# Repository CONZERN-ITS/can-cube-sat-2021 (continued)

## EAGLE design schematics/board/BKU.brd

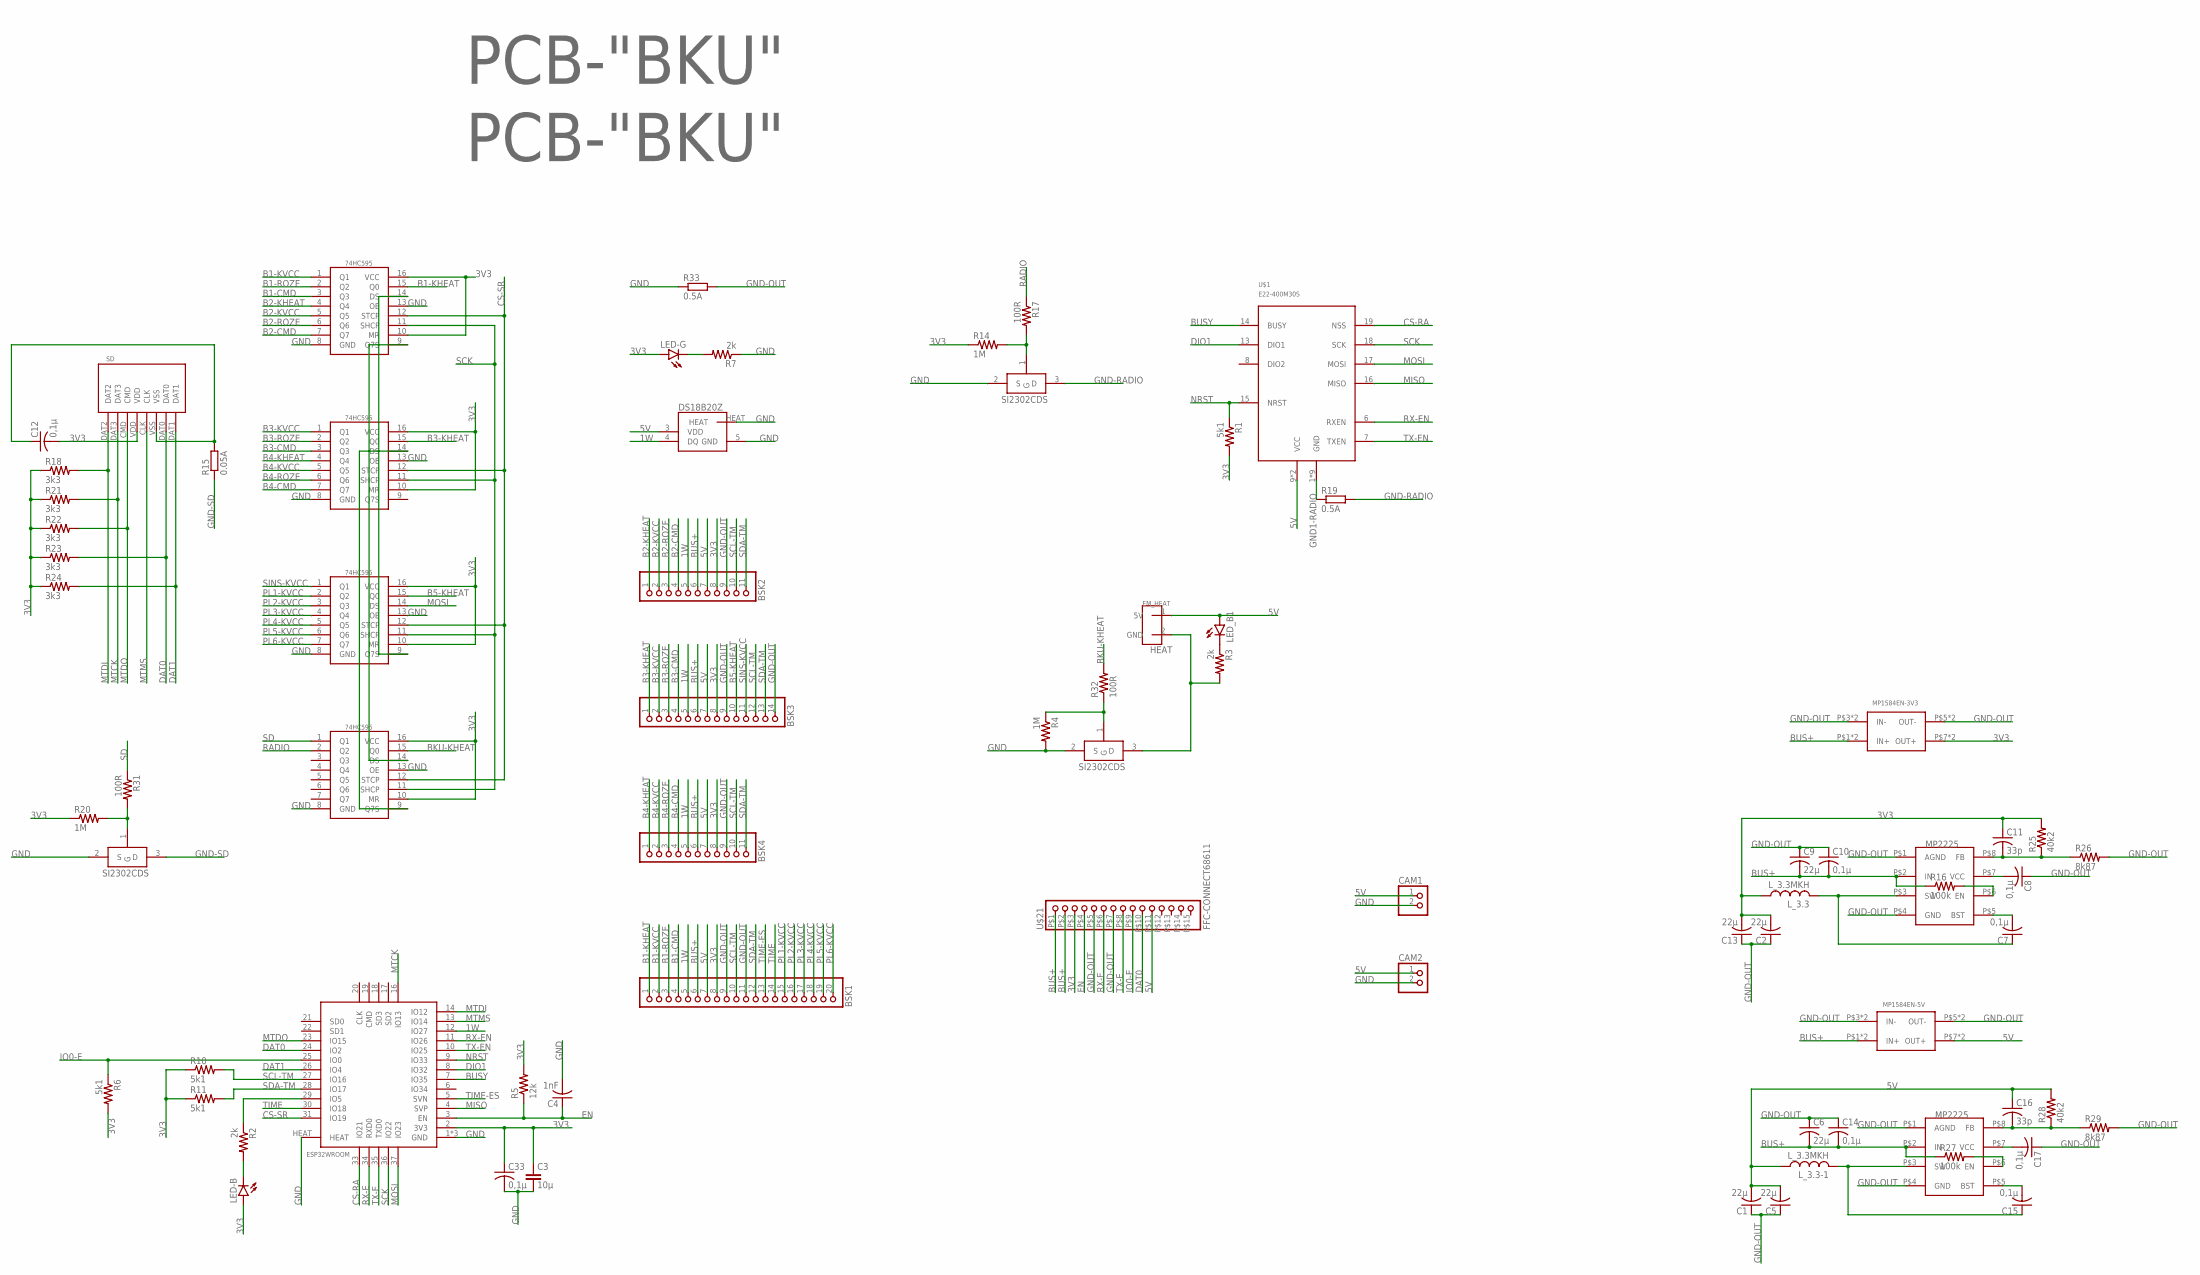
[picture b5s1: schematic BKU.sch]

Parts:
74HC595#1, 74HC595#2, 74HC595#3, 74HC595#4: 74HC595; TSSOP16
BSK1: PINHD-1X20; 1X20
BSK2, BSK4: PINHD-1X11; 1X11
BSK3: PINHD-1X14; 1X14
C1, C2, C5, C6, C9, C13: 22µ; C1206
C3: 10µ; C1206
C4: 1nF; C0603
C7, C8, C10, C12, C14, C15, C17, C33: 0,1µ; C0603
C11, C16: 33p; C0603
CAM1, CAM2: PINHD-1X2; 1X02
LED-B: LEDCHIPLED_0603; CHIPLED_0603
LED-G: LEDCHIPLED_0603; CHIPLED_0603
LED_B1: LEDCHIPLED_0603; CHIPLED_0603
L_3.3, L_3.3-1: L_3.3MKH; L_SPM5020
MP1584EN-3V3, MP1584EN-5V: MP1584-B
MP2225-3V3, MP2225-5V: MP2225; TSOT23-8
R1, R6, R10, R11: 5k1; R0603
R2, R3, R7: 2k; R0603
R4, R14, R20: 1M; R0603
R5: 12k; R0603
R15: 0.05A; R1210
R16, R27: 100k; R0603
R17, R31, R32: 100R; R0603
R18, R21, R22, R23, R24: 3k3; R0603
R19, R33: 0.5A; R1210
R25, R28: 40k2; R0603
R26, R29: 8k87; R0603
SD: SD
U$1: E22-400M30S
U$2, U$6: PCB-"BKU"; ITS-LOGO
U$3, U$4, U$23: SI2302CDS; SOT23-3
U$5: DS18B20Z; SOIC8+HEAT_S
U$13: ESP32WROOM
U$21: FFC-CONNECT68611; 68611
U$24: EM_HEAT

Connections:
1W: BSK1.5, BSK2.5, BSK3.5, BSK4.5, U$5.4 (DQ), U$13.12 (IO27)
3: R3.2, U$23.3 (D), U$24.2 (GND)
3V3: 74HC595#1.10 (MR), 74HC595#1.16 (VCC), 74HC595#2.10 (MR), 74HC595#2.16 (VCC), 74HC595#3.10 (MR), 74HC595#3.16 (VCC), 74HC595#4.10 (MR), 74HC595#4.16 (VCC), BSK1.8, BSK2.8, BSK3.8, BSK4.8, C2.2, C3.1, C11.1, C12.2, C13.2, C33.1, LED-B.A, LED-G.A, L_3.3.P$1 (1), MP1584EN-3V3.P$7 (OUT+), MP1584EN-3V3.P$8 (OUT+), R1.2, R5.2, R6.2, R10.1, R11.1, R14.1, R18.1, R20.1, R21.1, R22.1, R23.1, R24.1, R25.2, SD.VDD, U$13.2 (3V3), U$21.P$3 (3)
5V: BSK1.7, BSK2.7, BSK3.7, BSK4.7, C1.2, C5.2, C16.1, CAM1.1, CAM2.1, LED_B1.A, L_3.3-1.P$1 (1), MP1584EN-5V.P$7 (OUT+), MP1584EN-5V.P$8 (OUT+), R28.2, U$1.9 (VCC), U$1.10 (VCC), U$5.3 (VDD), U$21.P$11 (11), U$24.1 (5V)
B1-CMD: 74HC595#1.3 (Q3), BSK1.4
B1-KHEAT: 74HC595#1.15 (Q0), BSK1.1
B1-KVCC: 74HC595#1.1 (Q1), BSK1.2
B1-ROZE: 74HC595#1.2 (Q2), BSK1.3
B2-CMD: 74HC595#1.7 (Q7), BSK2.4
B2-KHEAT: 74HC595#1.4 (Q4), BSK2.1
B2-KVCC: 74HC595#1.5 (Q5), BSK2.2
B2-ROZE: 74HC595#1.6 (Q6), BSK2.3
B3-CMD: 74HC595#2.3 (Q3), BSK3.4
B3-KHEAT: 74HC595#2.15 (Q0), BSK3.1
B3-KVCC: 74HC595#2.1 (Q1), BSK3.2
B3-ROZE: 74HC595#2.2 (Q2), BSK3.3
B4-CMD: 74HC595#2.7 (Q7), BSK4.4
B4-KHEAT: 74HC595#2.4 (Q4), BSK4.1
B4-KVCC: 74HC595#2.5 (Q5), BSK4.2
B4-ROZE: 74HC595#2.6 (Q6), BSK4.3
B5-KHEAT: 74HC595#3.15 (Q0), BSK3.10
BKU-KHEAT: 74HC595#4.15 (Q0), R32.2
BUS+: BSK1.6, BSK2.6, BSK3.6, BSK4.6, C6.2, C9.2, C10.2, C14.2, MP1584EN-3V3.P$1 (IN+), MP1584EN-3V3.P$2 (IN+), MP1584EN-5V.P$1 (IN+), MP1584EN-5V.P$2 (IN+), MP2225-3V3.P$2 (IN), MP2225-5V.P$2 (IN), R16.1, R27.1, U$21.P$1 (1), U$21.P$2 (2)
BUSY: U$1.14 (BUSY), U$13.7 (IO35)
CS-RA: U$1.19 (NSS), U$13.33 (IO21)
CS-SR: 74HC595#1.12 (STCP), 74HC595#2.12 (STCP), 74HC595#3.12 (STCP), 74HC595#4.12 (STCP), U$13.31 (IO19)
DAT0: R23.2, SD.DAT0, U$13.24 (IO2), U$21.P$10 (10)
DAT1: R24.2, SD.DAT1, U$13.26 (IO4)
DIO1: U$1.13 (DIO1), U$13.8 (IO32)
EN: C4.1, R5.1, U$13.3 (EN), U$21.P$4 (4)
GND: 74HC595#1.8 (GND), 74HC595#1.13 (OE), 74HC595#2.8 (GND), 74HC595#2.13 (OE), 74HC595#3.8 (GND), 74HC595#3.13 (OE), 74HC595#4.8 (GND), 74HC595#4.13 (OE), C3.2, C4.2, C33.2, CAM1.2, CAM2.2, R4.2, R7.1, R33.1, U$3.2 (S), U$4.2 (S), U$5.5 (GND), U$5.HEAT, U$13.1 (GND), U$13.15 (GND), U$13.38 (GND), U$13.HEAT, U$23.2 (S)
GND1-RADIO: R19.1, U$1.1 (GND), U$1.2 (GND), U$1.3 (GND), U$1.4 (GND), U$1.5 (GND), U$1.11 (GND), U$1.12 (GND), U$1.20 (GND), U$1.22 (GND)
GND-OUT: BSK1.9, BSK1.11, BSK2.9, BSK3.9, BSK3.14, BSK4.9, C1.1, C2.1, C5.1, C6.1, C8.1, C9.1, C10.1, C13.1, C14.1, C17.1, MP1584EN-3V3.P$3 (IN-), MP1584EN-3V3.P$4 (IN-), MP1584EN-3V3.P$5 (OUT-), MP1584EN-3V3.P$6 (OUT-), MP1584EN-5V.P$3 (IN-), MP1584EN-5V.P$4 (IN-), MP1584EN-5V.P$5 (OUT-), MP1584EN-5V.P$6 (OUT-), MP2225-3V3.P$1 (AGND), MP2225-3V3.P$4 (GND), MP2225-5V.P$1 (AGND), MP2225-5V.P$4 (GND), R26.2, R29.2, R33.2, U$21.P$5 (5), U$21.P$7 (7)
GND-RADIO: R19.2, U$4.3 (D)
GND-SD: R15.1, U$3.3 (D)
IO0-E: R6.1, U$13.25 (IO0), U$21.P$9 (9)
IO1: R2.1, U$13.29 (IO5)
MISO: U$1.16 (MISO), U$13.4 (SVP)
MOSI: 74HC595#3.14 (DS), U$1.17 (MOSI), U$13.37 (IO23)
MTCK: R21.2, SD.DAT3, U$13.16 (IO13)
MTDI: R18.2, SD.DAT2, U$13.14 (IO12)
MTDO: R22.2, SD.CMD, U$13.23 (IO15)
MTMS: SD.CLK, U$13.13 (IO14)
unnamed: 74HC595#1.9 (Q7S), 74HC595#4.14 (DS)
unnamed: LED_B1.C, R3.1
unnamed: LED-G.C, R7.2
unnamed: LED-B.C, R2.2
unnamed: C12.1, R15.2, SD.VSS
unnamed: R14.2, R17.2, U$4.1 (G)
unnamed: 74HC595#2.14 (DS), 74HC595#4.9 (Q7S)
unnamed: C15.1, L_3.3-1.P$2 (2), MP2225-5V.P$3 (SW)
unnamed: C15.2, MP2225-5V.P$5 (BST)
unnamed: MP2225-5V.P$6 (EN), R27.2
unnamed: R20.2, R31.2, U$3.1 (G)
unnamed: C17.2, MP2225-5V.P$7 (VCC)
unnamed: C7.2, MP2225-3V3.P$5 (BST)
unnamed: C7.1, L_3.3.P$2 (2), MP2225-3V3.P$3 (SW)
unnamed: MP2225-3V3.P$6 (EN), R16.2
unnamed: C8.2, MP2225-3V3.P$7 (VCC)
unnamed: 74HC595#1.14 (DS), 74HC595#3.9 (Q7S)
unnamed: C11.2, MP2225-3V3.P$8 (FB), R25.1, R26.1
unnamed: C16.2, MP2225-5V.P$8 (FB), R28.1, R29.1
unnamed: R4.1, R32.1, U$23.1 (G)
NRST: R1.1, U$1.15 (NRST), U$13.9 (IO33)
PL1-KVCC: 74HC595#3.2 (Q2), BSK1.15
PL2-KVCC: 74HC595#3.3 (Q3), BSK1.16
PL3-KVCC: 74HC595#3.4 (Q4), BSK1.17
PL4-KVCC: 74HC595#3.5 (Q5), BSK1.18
PL5-KVCC: 74HC595#3.6 (Q6), BSK1.19
PL6-KVCC: 74HC595#3.7 (Q7), BSK1.20
RADIO: 74HC595#4.2 (Q2), R17.1
RX-E: U$13.34 (RXD0), U$21.P$6 (6)
RX-EN: U$1.6 (RXEN), U$13.11 (IO26)
SCK: 74HC595#1.11 (SHCP), 74HC595#2.11 (SHCP), 74HC595#3.11 (SHCP), 74HC595#4.11 (SHCP), U$1.18 (SCK), U$13.36 (IO22)
SCL-TM: BSK1.10, BSK2.10, BSK3.12, BSK4.10, R10.2, U$13.27 (IO16)
SD: 74HC595#4.1 (Q1), R31.1
SDA-TM: BSK1.12, BSK2.11, BSK3.13, BSK4.11, R11.2, U$13.28 (IO17)
SINS-KVCC: 74HC595#3.1 (Q1), BSK3.11
TIME: BSK1.14, U$13.30 (IO18)
TIME-ES: BSK1.13, U$13.5 (SVN)
TX-E: U$13.35 (TXD0), U$21.P$8 (8)
TX-EN: U$1.7 (TXEN), U$13.10 (IO25)

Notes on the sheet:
HEAT

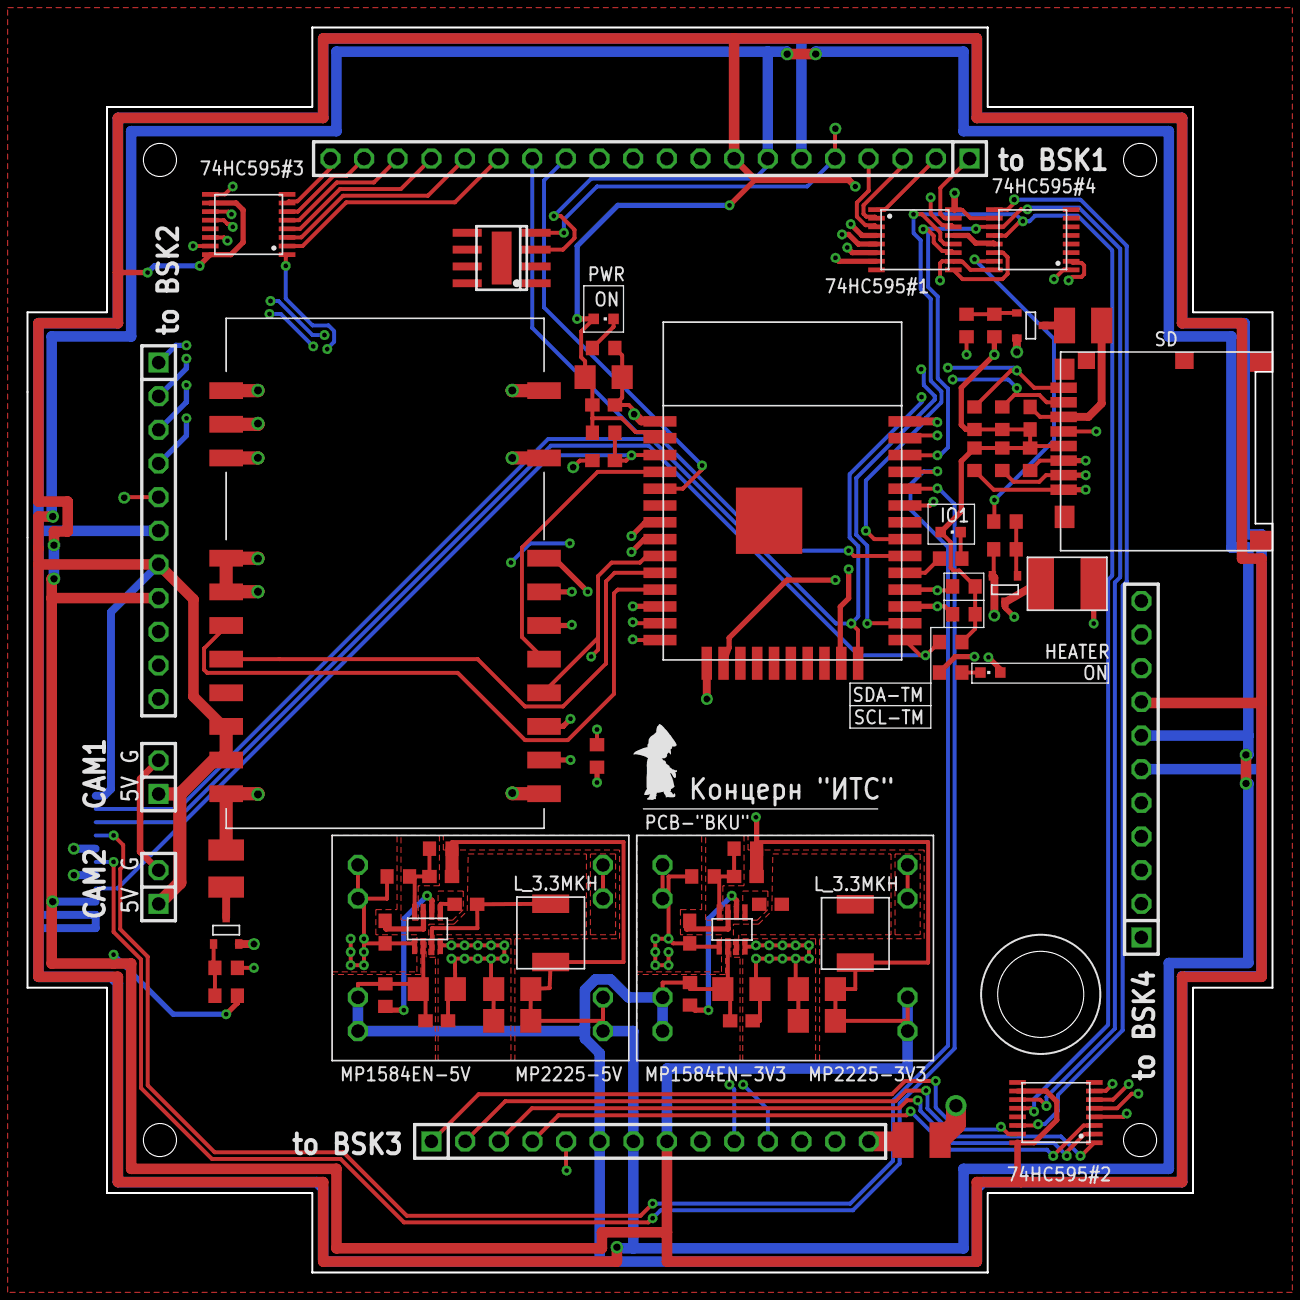
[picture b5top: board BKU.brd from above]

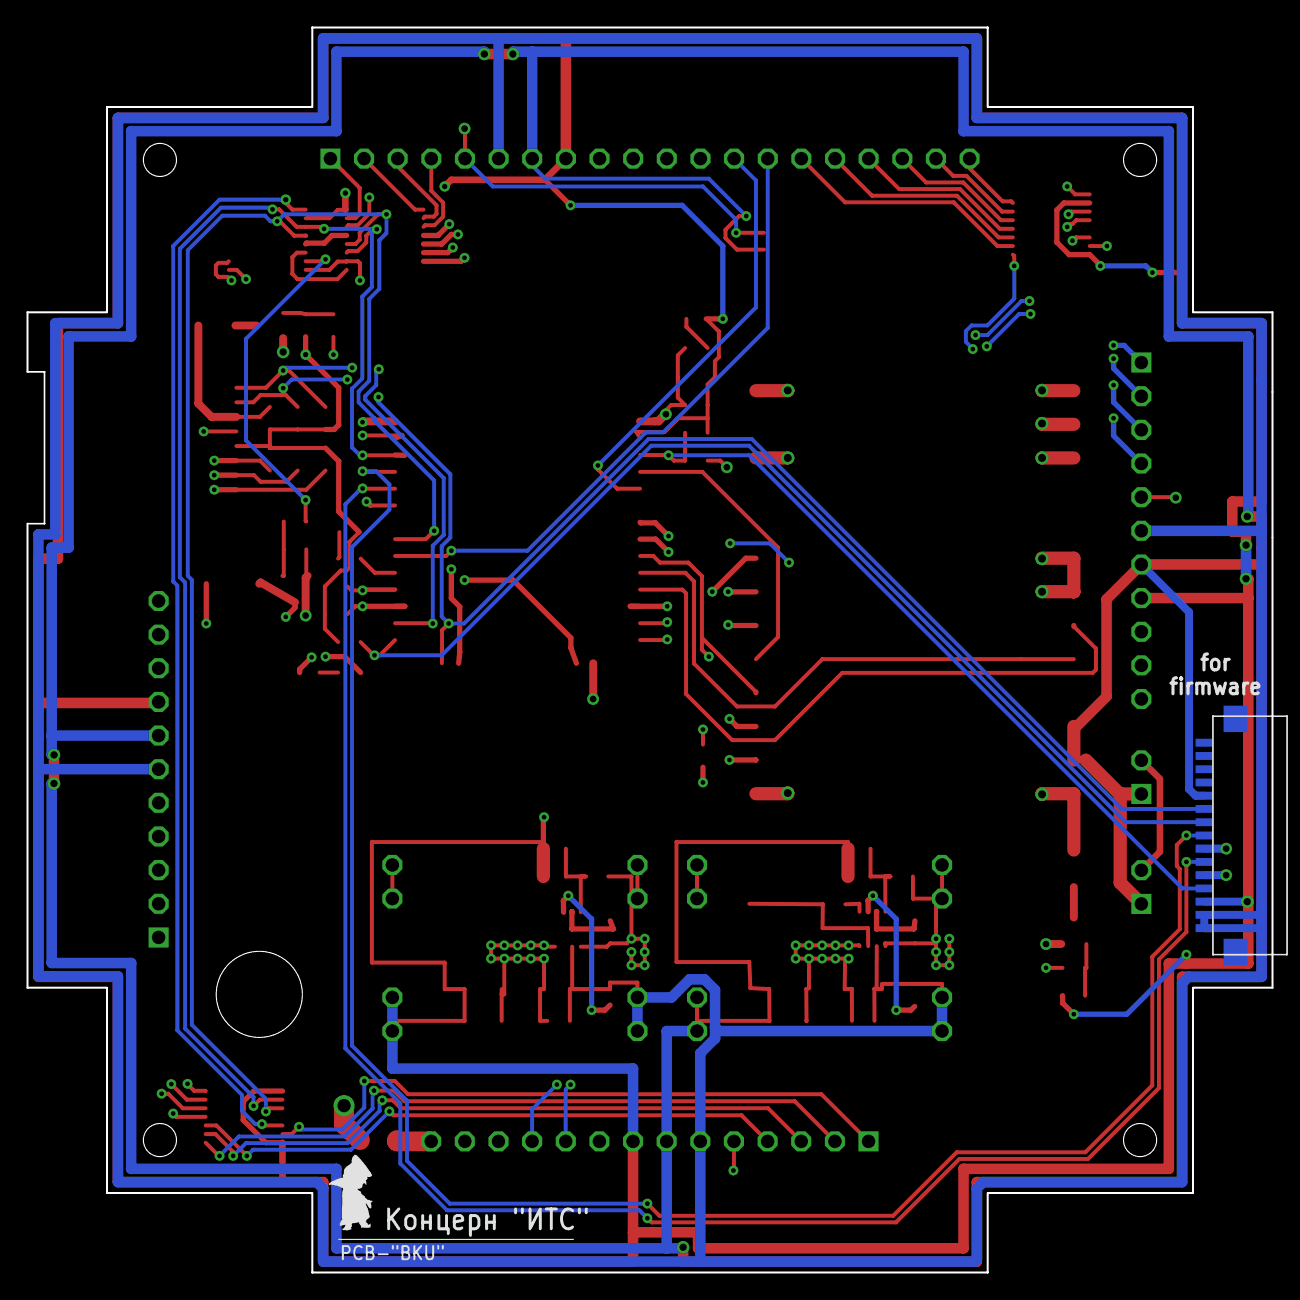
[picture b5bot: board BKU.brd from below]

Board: 4 copper layers, 94.0 x 94.0 mm, 76 parts (2 on the bottom side), 82 nets.

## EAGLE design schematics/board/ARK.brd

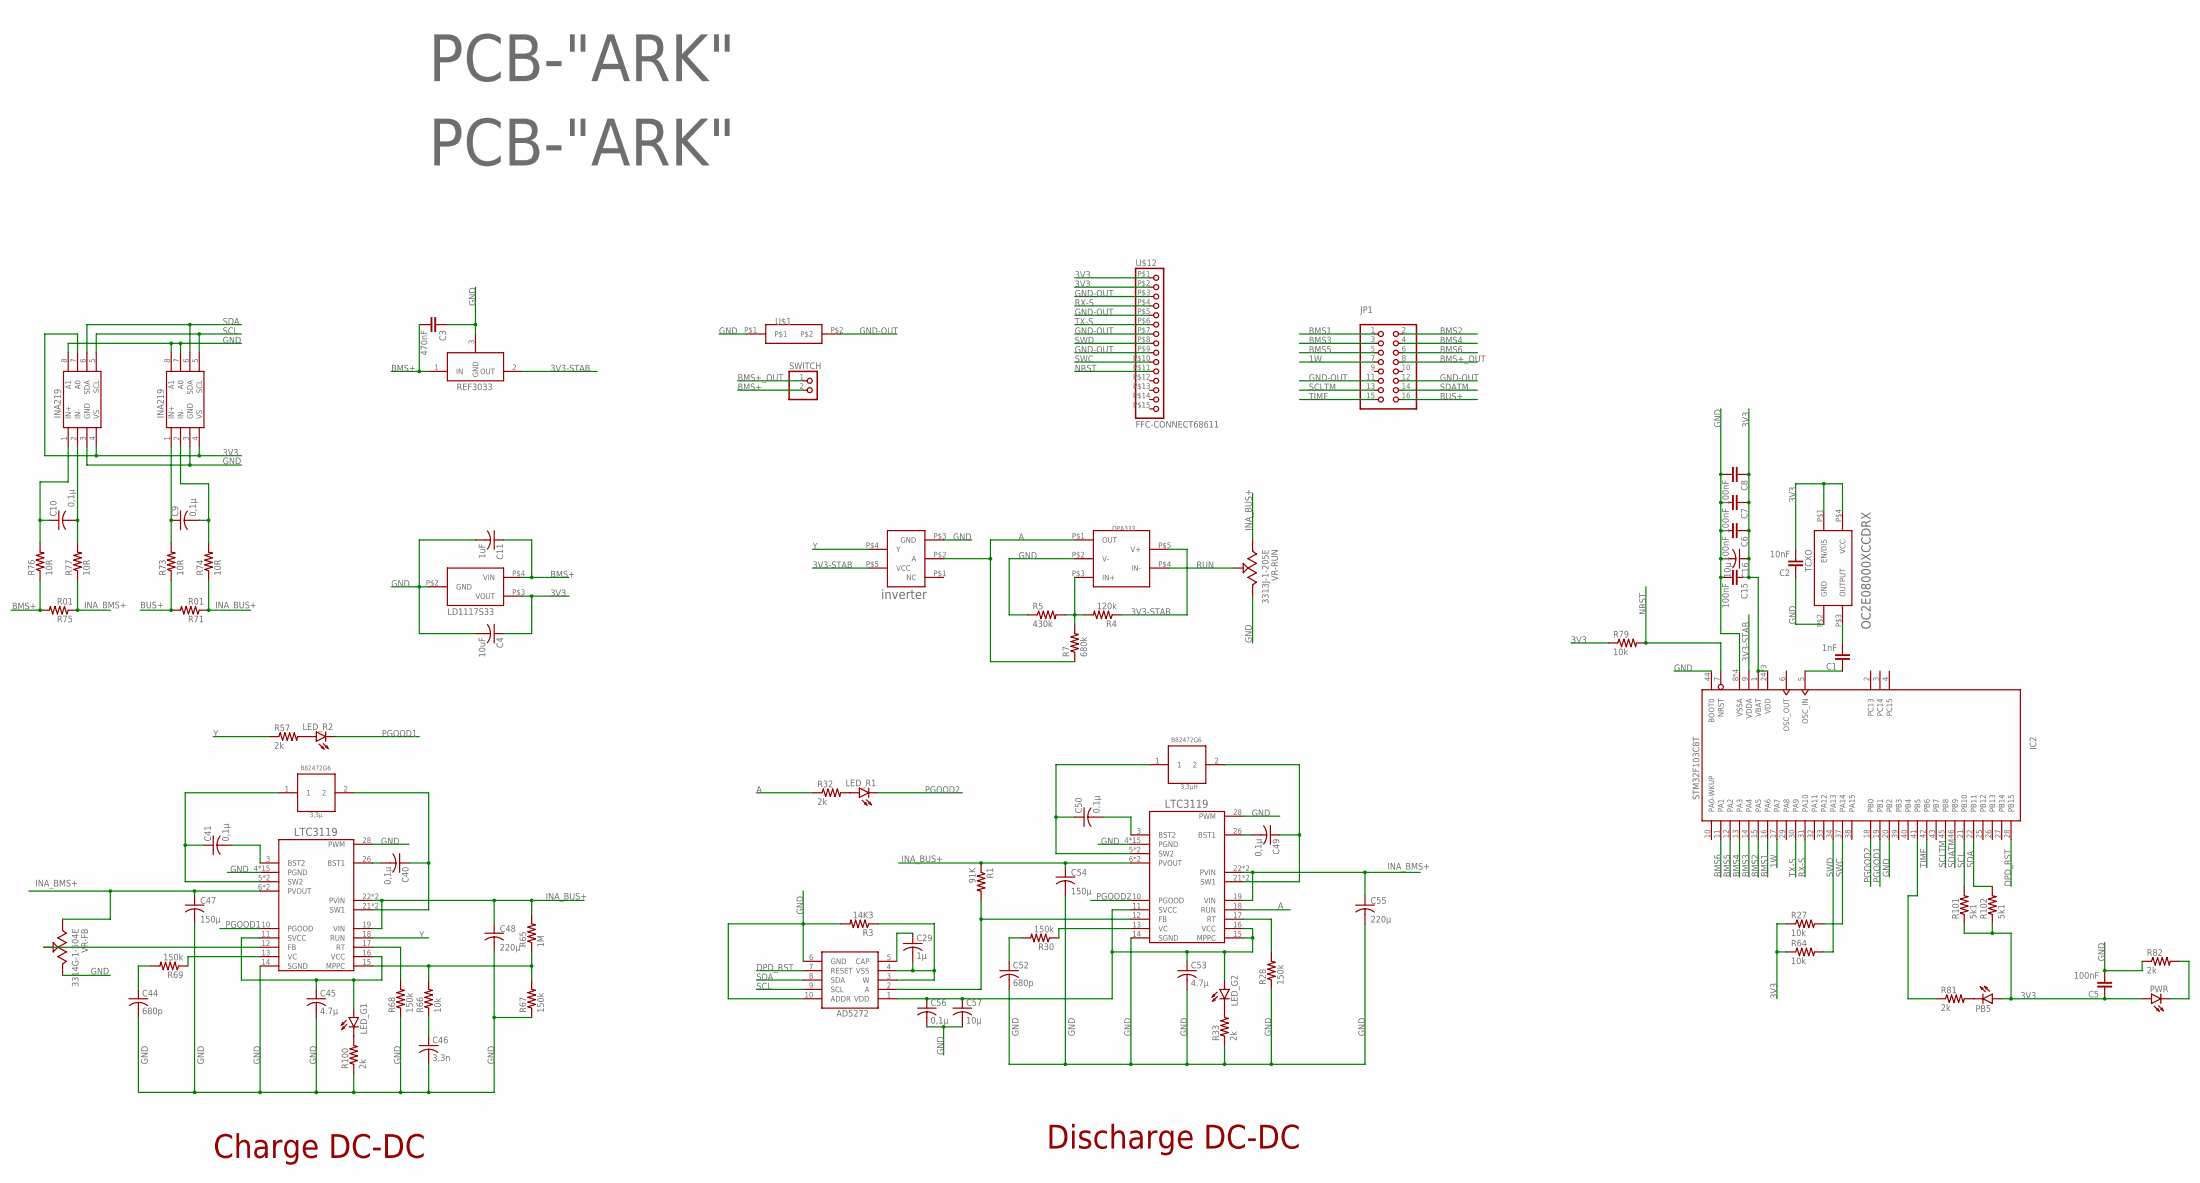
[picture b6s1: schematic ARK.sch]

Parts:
3,3µH: 3,3µ; B82472G6
3,3µH1: 3,3µH; B82472G6
AD5272#2: AD5272; MSOP10
C1: 1nF; C0603
C2: 10nF; C0603
C3: 470nF; C0603
C4: 10uF; ECAP-SMD-D4
C5, C6, C7, C8, C15: 100nF; C0603
C9, C10, C40, C41, C49, C50, C56: 0,1µ; C0603
C11: 1uF; ECAP-SMD-D4
C16, C57: 10µ; C1206
C29: 1µ; C0603
C44, C52: 680p; C0603
C45, C53: 4.7µ; C1206
C46: 3,3n; C0603
C47, C54: 150µ; ECAP150-CMD
C48, C55: 220µ; ECAP220-CMD
IC2: STM32F103C8T; LQFP48
INA219#1, INA219#2: INA219AID; SOT23-8
INVERT: INVERTER.; SC70
JP1: PINHD-2X8; 2X08
LD1117S33: LD1117S33; SOT223
LED_G1, LED_G2: LEDCHIPLED_0603; CHIPLED_0603
LED_R1, LED_R2: LEDCHIPLED_0603; CHIPLED_0603
OPA: OPA333; SOT23-5
PB5: LEDCHIPLED_0603; CHIPLED_0603
PWR: LEDCHIPLED_0603; CHIPLED_0603
R1: 91K; R0603
R3: 14K3; R0603
R4: 120k; R0603
R5: 430k; R0603
R7: 680k; R0603
R27, R64, R66, R79: 10k; R0603
R28, R30, R67, R68, R69: 150k; R0603
R32, R33, R57, R81, R82, R100: 2k; R0603
R65: 1M; R0603
R71, R75: R01; R2512
R73, R74, R76, R77: 10R; R0603
R101, R102: 5k1; R0603
REF3033: REF3033; SOT23-3
SWITCH: PINHD-1X2; 1X02
TCXO: OC2E08000XCCDRX
U$1: MF-R400
U$3, U$4: PCB-"ARK"; ITS-LOGO
U$12: FFC-CONNECT68611; 68611
U$23, U$59: LTC31191; LTC3119+VIA
VR-FB: 3314G-1-504E; TRIM_3314G-1-504E
VR-RUN: 3313J-1-205E; TRIM_3313J-1-205E

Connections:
1W: IC2.17 (PA7), JP1.7
3V3: C2.2, C4.P+ (1), C5.1, C6.1, C7.1, C8.1, C15.1, C16.1, IC2.1 (VBAT), IC2.24 (VDD), IC2.36 (VDD), IC2.48 (VDD), INA219#1.4 (VS), INA219#2.4 (VS), INA219#2.7 (A0), LD1117S33.P$3 (VOUT), PB5.A, PWR.A, R27.1, R64.1, R79.1, R101.1, R102.1, TCXO.P$1 (EN/DIS), TCXO.P$4 (VCC), U$12.P$1 (1), U$12.P$2 (2)
3V3-STAB: IC2.9 (VDDA), INVERT.P$5 (VCC), OPA.P$5 (V+), R4.1, REF3033.2 (OUT)
90: R65.1, R66.2, R67.2, U$59.15 (MPPC)
A: INVERT.P$2 (A), OPA.P$1 (OUT), R7.1, R32.1, U$23.18 (RUN)
BMS1: IC2.16 (PA6), JP1.1
BMS2: IC2.15 (PA5), JP1.2
BMS3: IC2.14 (PA4), JP1.3
BMS4: IC2.13 (PA3), JP1.4
BMS5: IC2.12 (PA2), JP1.5
BMS6: IC2.11 (PA1), JP1.6
BMS+: C3.2, C11.P+ (1), LD1117S33.P$4 (VIN), R75.2, R76.1, REF3033.1 (IN), SWITCH.2
BMS+_OUT: JP1.8, SWITCH.1
BUS+: JP1.16, R71.2, R73.1
DPD_RST: AD5272#2.7 (RESET), IC2.28 (PB15)
GND: AD5272#2.6 (GND), AD5272#2.10 (ADDR), C2.1, C3.1, C4.P- (2), C5.2, C6.2, C7.2, C8.2, C11.P- (2), C15.2, C16.2, C44.2, C45.2, C46.2, C47.P$2 (2), C48.P$2 (2), C52.2, C53.2, C54.P$2 (2), C55.P$2 (2), C56.2, C57.2, IC2.8 (VSSA), IC2.20 (PB2), IC2.23 (VSSA), IC2.35 (VSSA), IC2.44 (BOOT0), IC2.47 (VSSA), INA219#1.3 (GND), INA219#1.7 (A0), INA219#1.8 (A1), INA219#2.3 (GND), INA219#2.8 (A1), INVERT.P$3 (GND), LD1117S33.P$2 (GND), OPA.P$2 (V-), R3.2, R5.1, R28.1, R33.1, R67.1, R68.1, R82.1, R100.1, REF3033.3 (GND), TCXO.P$2 (GND), U$1.P$1, U$23.4 (PGND), U$23.9 (PGND), U$23.14 (SGND), U$23.20 (PGND), U$23.25 (PGND), U$23.28 (PWM), U$23.29 (PGND), U$23.P$1 (PGND), U$23.P$2 (PGND), U$23.P$3 (PGND), U$23.P$4 (PGND), U$23.P$5 (PGND), U$23.P$6 (PGND), U$23.P$7 (PGND), U$23.P$8 (PGND), U$23.P$9 (PGND), U$23.P$10 (PGND), U$59.4 (PGND), U$59.9 (PGND), U$59.14 (SGND), U$59.20 (PGND), U$59.25 (PGND), U$59.28 (PWM), U$59.29 (PGND), U$59.P$1 (PGND), U$59.P$2 (PGND), U$59.P$3 (PGND), U$59.P$4 (PGND), U$59.P$5 (PGND), U$59.P$6 (PGND), U$59.P$7 (PGND), U$59.P$8 (PGND), U$59.P$9 (PGND), U$59.P$10 (PGND), VR-FB.3 (CW), VR-RUN.3 (CW)
GND-OUT: JP1.11, JP1.12, U$1.P$2, U$12.P$3 (3), U$12.P$5 (5), U$12.P$7 (7), U$12.P$9 (9)
INA_BMS+: C47.P$1 (1), C55.P$1 (1), R75.1, R77.1, U$23.19 (VIN), U$23.22 (PVIN), U$23.23 (PVIN), U$59.6 (PVOUT), U$59.7 (PVOUT), VR-FB.1 (CCW)
INA_BUS+: C48.P$1 (1), C54.P$1 (1), R1.1, R65.2, R71.1, R74.1, U$23.6 (PVOUT), U$23.7 (PVOUT), U$59.19 (VIN), U$59.22 (PVIN), U$59.23 (PVIN), VR-RUN.1 (CCW)
unnamed: C1.1, IC2.5 (OSC_IN)
unnamed: OPA.P$3 (IN+), R4.2, R5.2, R7.2
unnamed: AD5272#2.2 (A), R1.2, U$23.12 (FB)
unnamed: C1.2, TCXO.P$3 (OUTPUT)
unnamed: C9.2, INA219#1.2 (IN-), R74.2
unnamed: PB5.C, R81.2
unnamed: AD5272#2.3 (W), AD5272#2.4 (VSS), C29.2, R3.1
unnamed: AD5272#2.5 (CAP), C29.1
unnamed: 3,3µH1.2, C49.1, U$23.21 (SW1), U$23.24 (SW1)
unnamed: 3,3µH1.1, C50.1, U$23.5 (SW2), U$23.8 (SW2)
unnamed: R28.2, U$23.17 (RT)
unnamed: C49.2, U$23.26 (BST1)
unnamed: R30.1, U$23.13 (VC)
unnamed: C52.1, R30.2
unnamed: C50.2, U$23.3 (BST2)
unnamed: LED_R1.A, R32.2
unnamed: LED_R2.A, R57.2
unnamed: U$59.12 (FB), VR-FB.2 (WIPER)
unnamed: LED_G1.C, R100.2
unnamed: LED_G2.C, R33.2
unnamed: C41.2, U$59.3 (BST2)
unnamed: 3,3µH.2, C40.1, U$59.21 (SW1), U$59.24 (SW1)
unnamed: 3,3µH.1, C41.1, U$59.5 (SW2), U$59.8 (SW2)
unnamed: R69.1, U$59.13 (VC)
unnamed: C44.1, R69.2
unnamed: C46.1, R66.1
unnamed: R68.2, U$59.17 (RT)
unnamed: C40.2, U$59.26 (BST1)
unnamed: C9.1, INA219#1.1 (IN+), R73.2
unnamed: C10.1, INA219#2.1 (IN+), R76.2
unnamed: C10.2, INA219#2.2 (IN-), R77.2
unnamed: PWR.C, R82.2
unnamed: IC2.41 (PB5), R81.1
unnamed: AD5272#2.1 (VDD), C53.1, C56.1, C57.1, LED_G2.A, U$23.11 (SVCC), U$23.15 (MPPC), U$23.16 (VCC)
unnamed: C45.1, LED_G1.A, U$59.11 (SVCC), U$59.16 (VCC)
NRST: IC2.7 (NRST), R79.2, U$12.P$11 (11)
PGOOD1: IC2.19 (PB1), LED_R2.C, U$59.10 (PGOOD)
PGOOD2: IC2.18 (PB0), LED_R1.C, U$23.10 (PGOOD)
RUN: OPA.P$4 (IN-), VR-RUN.2 (WIPER)
RX-S: IC2.31 (PA10), U$12.P$4 (4)
SCL: AD5272#2.9 (SCL), IC2.21 (PB10), INA219#1.5 (SCL), INA219#2.5 (SCL), R101.2
SCLTM: IC2.45 (PB8), JP1.13
SDA: AD5272#2.8 (SDA), IC2.22 (PB11), INA219#1.6 (SDA), INA219#2.6 (SDA), R102.2
SDATM: IC2.46 (PB9), JP1.14
SWC: IC2.37 (PA14), R27.2, U$12.P$10 (10)
SWD: IC2.34 (PA13), R64.2, U$12.P$8 (8)
TIME: IC2.42 (PB6), JP1.15
TX-S: IC2.30 (PA9), U$12.P$6 (6)
Y: INVERT.P$4 (Y), R57.1, U$59.18 (RUN)

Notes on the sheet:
Charge DC-DC
Discharge DC-DC

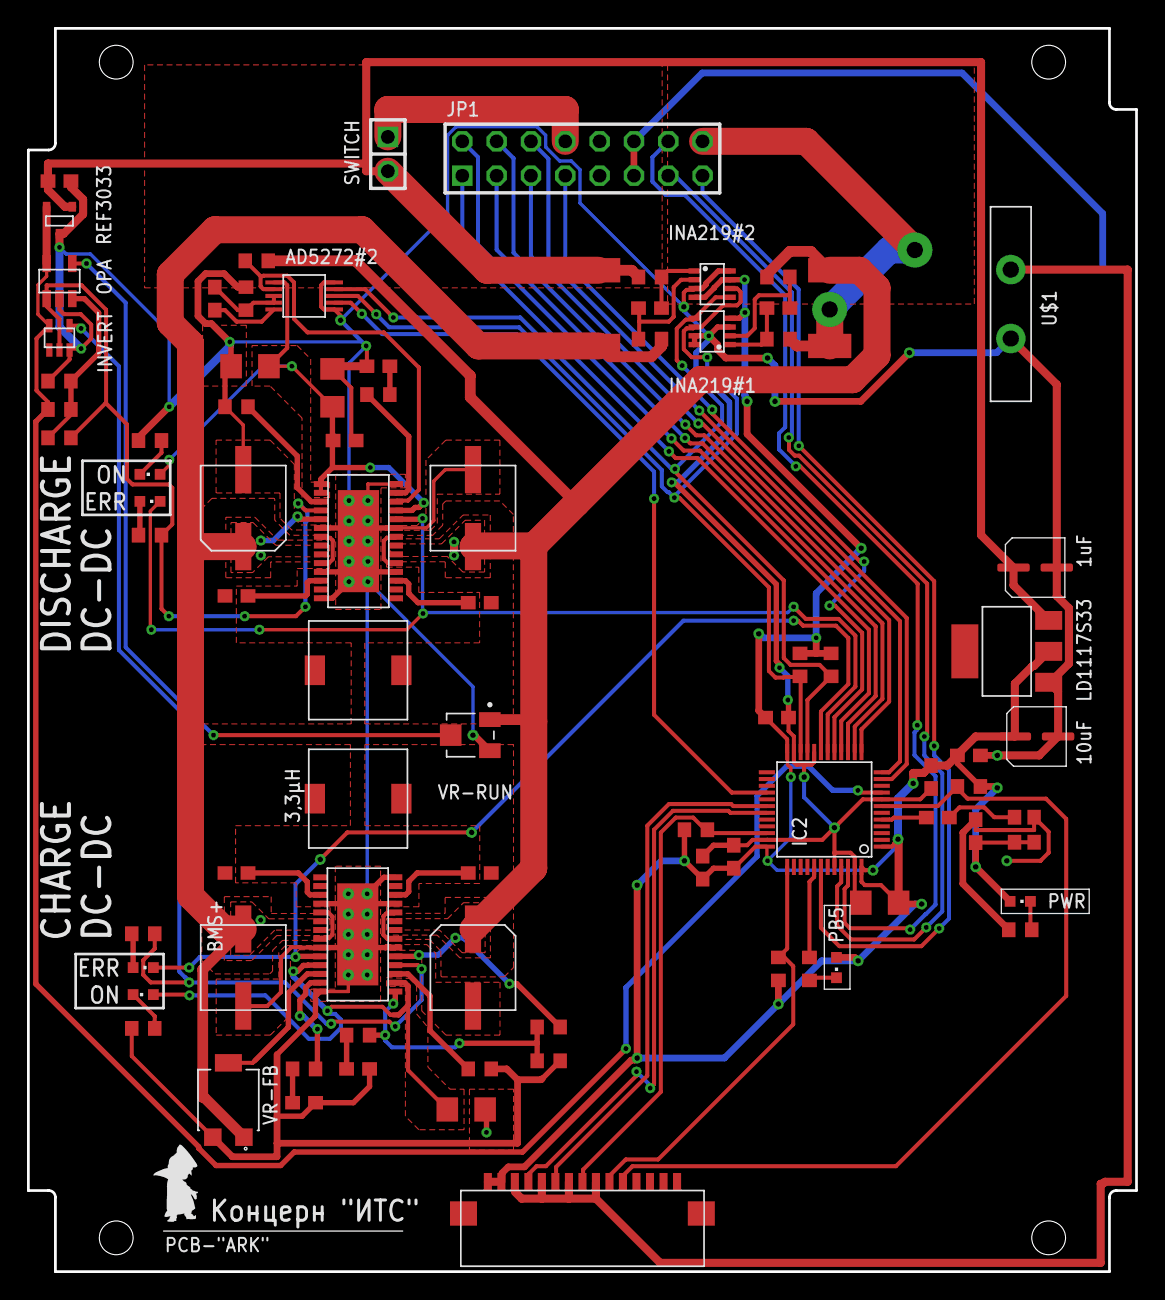
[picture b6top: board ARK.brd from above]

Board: 2 copper layers, 82.0 x 92.0 mm, 85 parts (1 on the bottom side), 68 nets.
